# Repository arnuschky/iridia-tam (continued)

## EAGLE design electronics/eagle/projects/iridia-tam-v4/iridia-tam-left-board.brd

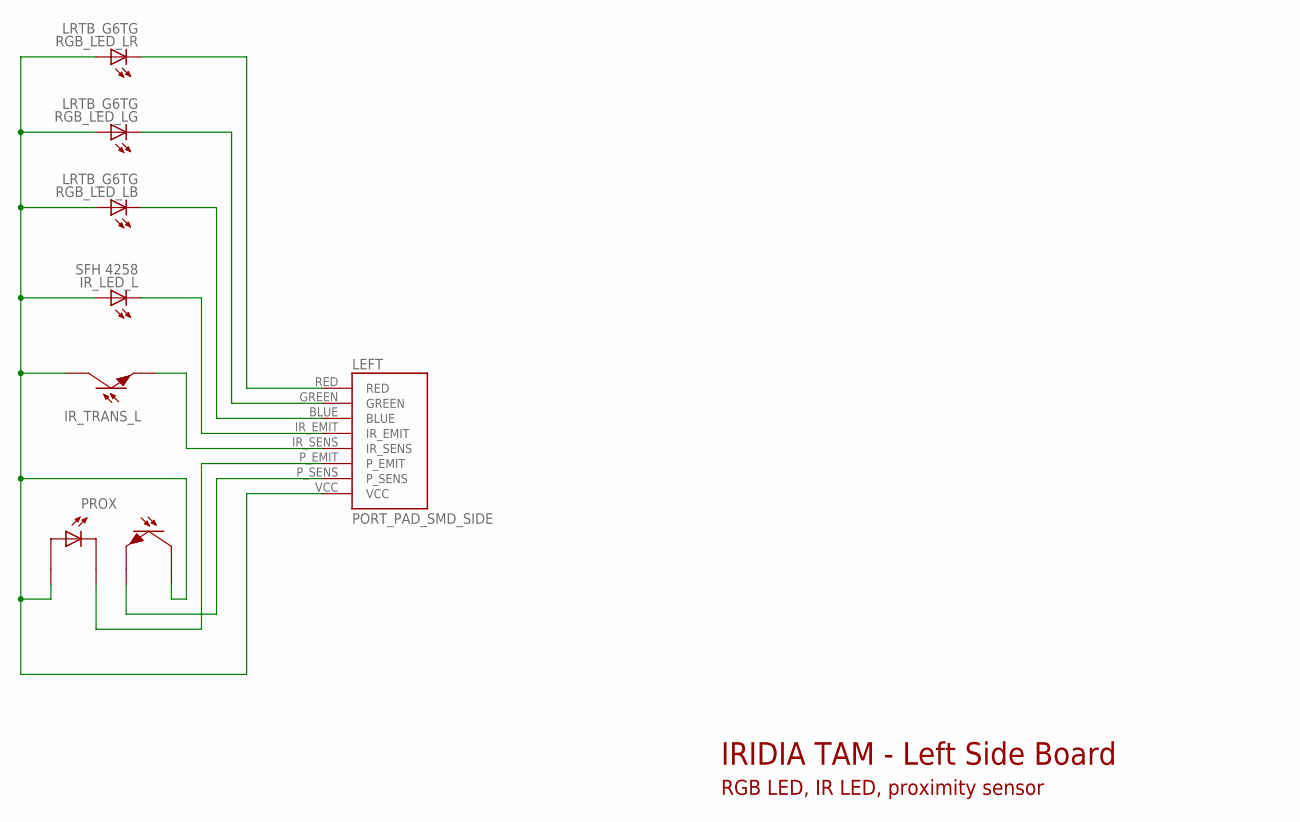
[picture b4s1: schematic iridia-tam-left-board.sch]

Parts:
IR_LED_L: SFH 4258; P-LCC-4-1C-3A
IR_TRANS_L: SFH 320 FA; P-LCC-2-TRANS
LEFT: PORT_PAD_SMD_SIDE
PROX: TCRT1000; TCRT1000_TH
RGB_LED_L: LRTB_G6TG; P-LCC-6_TOPLED

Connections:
BLUE_L: LEFT.BLUE, RGB_LED_L.C3 (C)
GREEN_L: LEFT.GREEN, RGB_LED_L.C2 (C)
IR_EMIT_L: IR_LED_L.C@1 (C), LEFT.IR_EMIT
IR_SENSE_L: IR_TRANS_L.E, LEFT.IR_SENS
PROX_EMIT: LEFT.P_EMIT, PROX.CAT
PROX_SENSE: LEFT.P_SENS, PROX.E
RED_L: LEFT.RED, RGB_LED_L.C1 (C)
VCC: IR_LED_L.A@2 (A), IR_LED_L.A@3 (A), IR_LED_L.A@4 (A), IR_TRANS_L.COL, LEFT.VCC, PROX.A, PROX.COL, RGB_LED_L.A1 (A), RGB_LED_L.A2 (A), RGB_LED_L.A3 (A)

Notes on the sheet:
IRIDIA TAM - Left Side Board
RGB LED, IR LED, proximity sensor

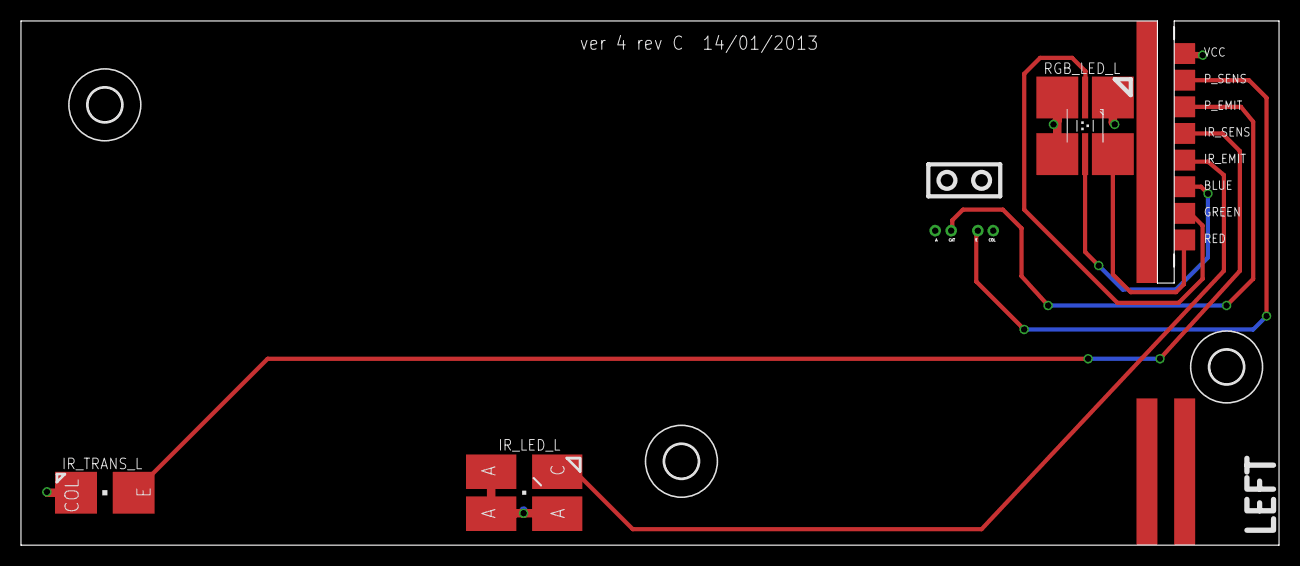
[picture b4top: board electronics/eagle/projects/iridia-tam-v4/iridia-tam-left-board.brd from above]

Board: 2 copper layers, 120.0 x 50.0 mm, 8 parts (0 on the bottom side), 8 nets.

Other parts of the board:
U$1, U$2, U$3: 3,2

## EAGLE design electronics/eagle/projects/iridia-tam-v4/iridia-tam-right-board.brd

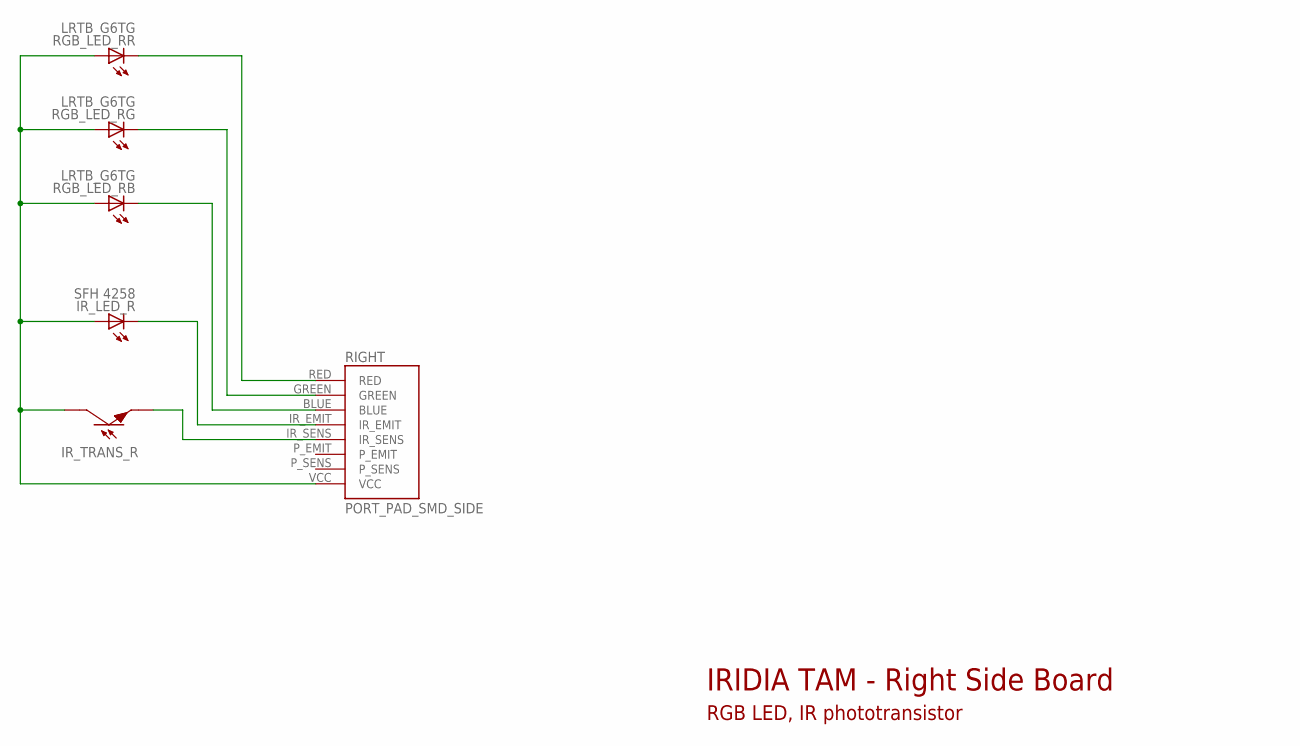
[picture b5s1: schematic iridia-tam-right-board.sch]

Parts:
IR_LED_R: SFH 4258; P-LCC-4-1C-3A
IR_TRANS_R: SFH 320 FA; P-LCC-2-TRANS
RGB_LED_R: LRTB_G6TG; P-LCC-6_TOPLED
RIGHT: PORT_PAD_SMD_SIDE

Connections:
BLUE_R: RGB_LED_R.C3 (C), RIGHT.BLUE
GREEN_R: RGB_LED_R.C2 (C), RIGHT.GREEN
IR_EMIT_R: IR_LED_R.C@1 (C), RIGHT.IR_EMIT
IR_SENSE_R: IR_TRANS_R.E, RIGHT.IR_SENS
RED_R: RGB_LED_R.C1 (C), RIGHT.RED
VCC: IR_LED_R.A@2 (A), IR_LED_R.A@3 (A), IR_LED_R.A@4 (A), IR_TRANS_R.COL, RGB_LED_R.A1 (A), RGB_LED_R.A2 (A), RGB_LED_R.A3 (A), RIGHT.VCC

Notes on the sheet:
IRIDIA TAM - Right Side Board
RGB LED, IR phototransistor

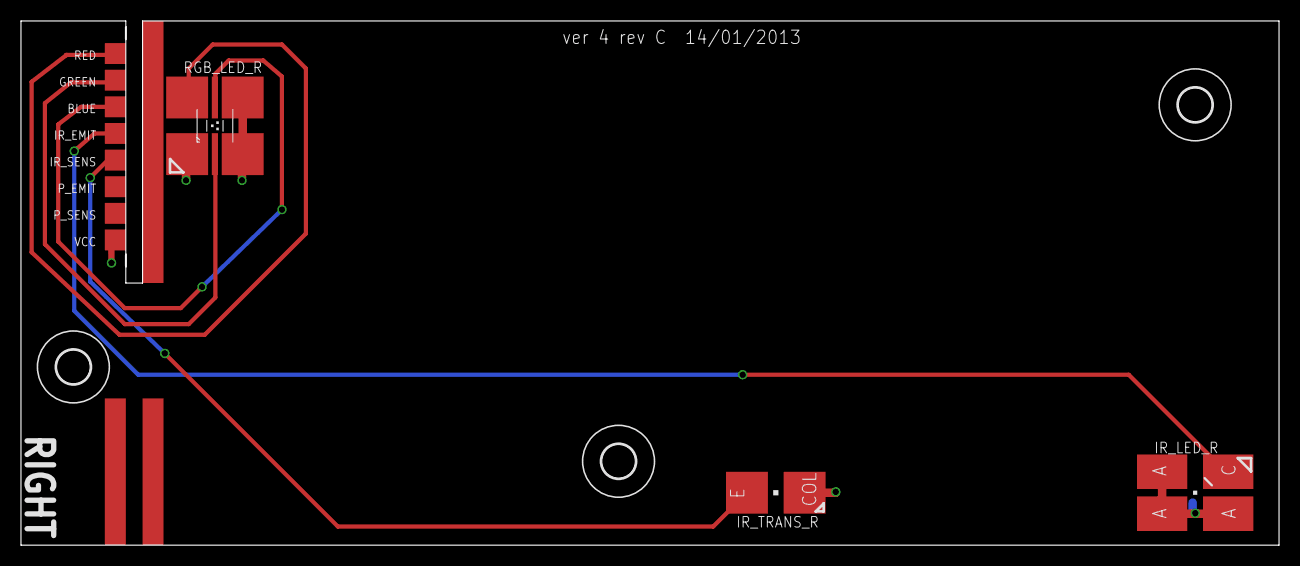
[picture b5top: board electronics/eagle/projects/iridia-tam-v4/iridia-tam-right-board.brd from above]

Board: 2 copper layers, 120.0 x 50.0 mm, 7 parts (0 on the bottom side), 6 nets.

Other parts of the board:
U$1, U$2, U$3: 3,2

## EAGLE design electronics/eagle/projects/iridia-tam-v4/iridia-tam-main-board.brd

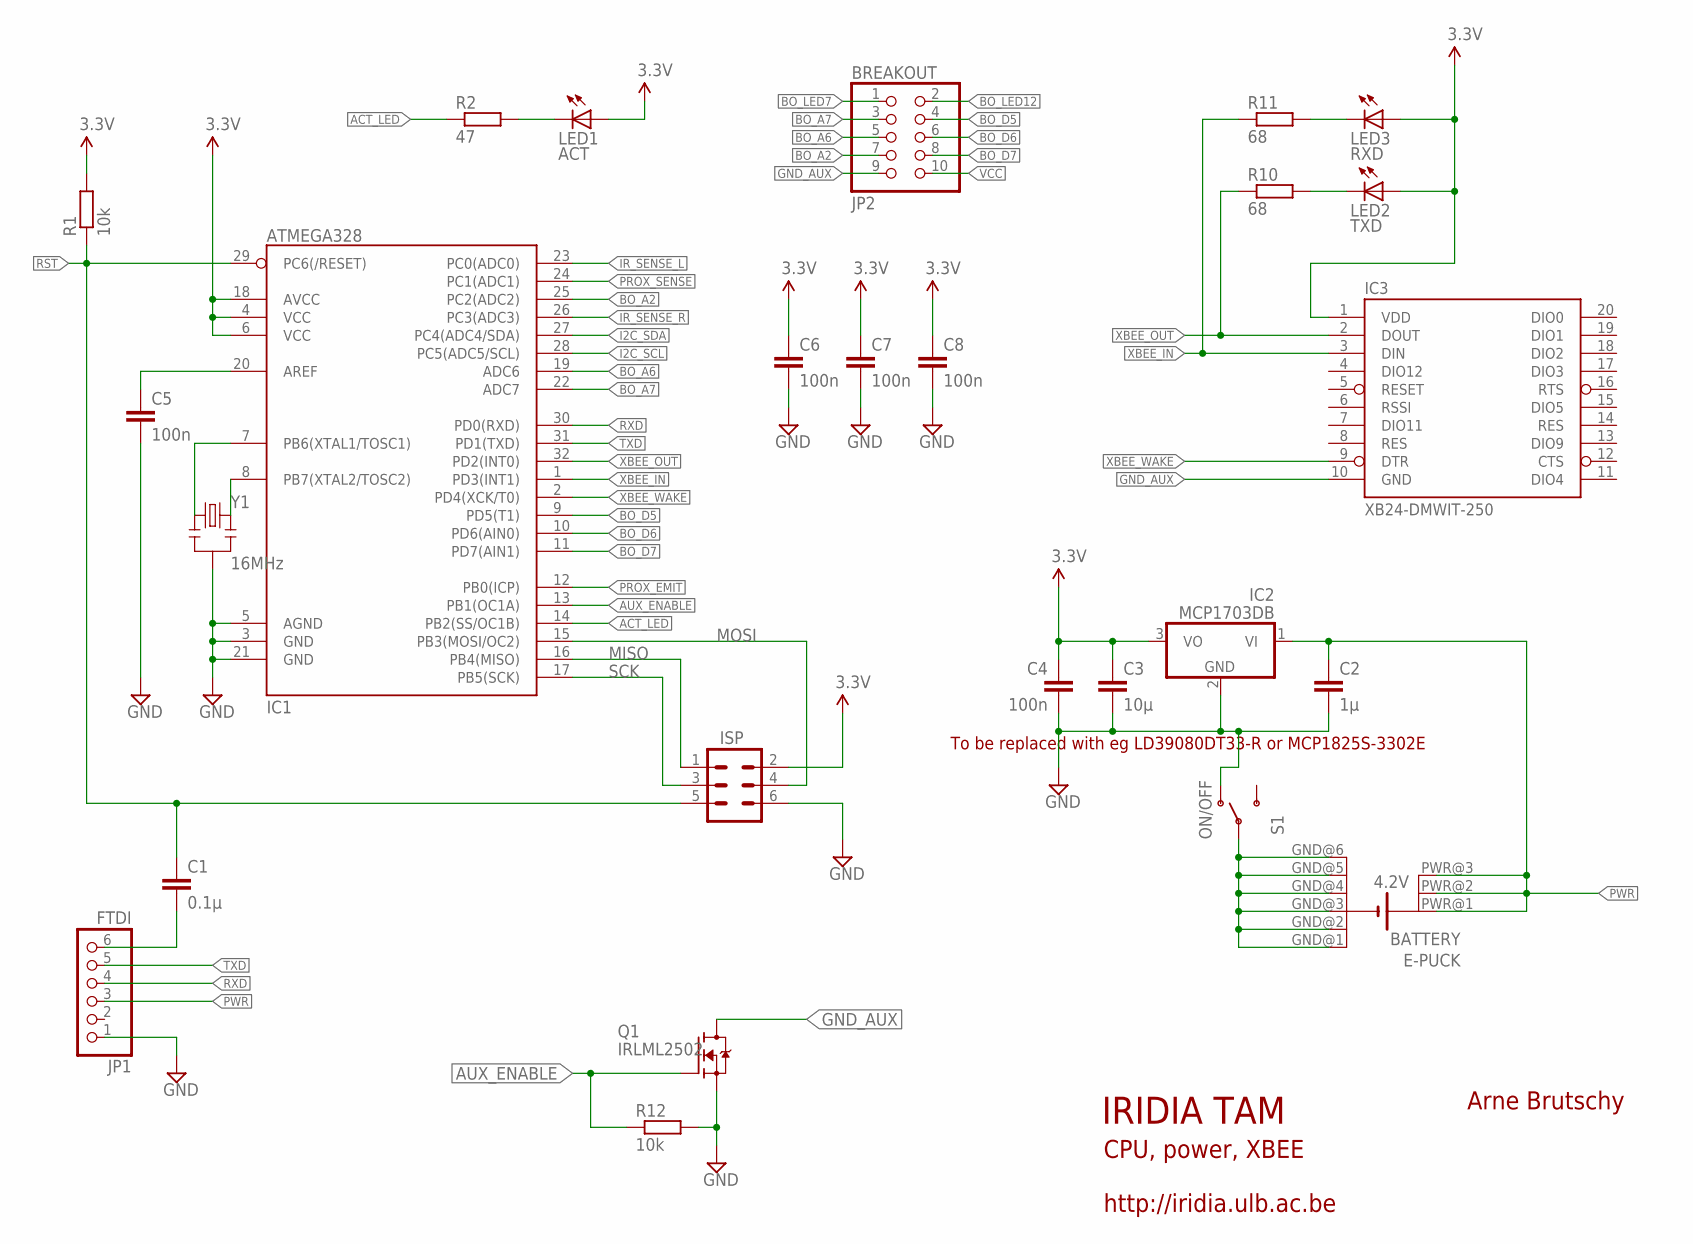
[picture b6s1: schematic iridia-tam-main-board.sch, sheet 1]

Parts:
BREAKOUT: JP2; 2X05SMD
C1: 0.1µ; 0805
C2: 1µ; 0805
C3: 10µ; 0805
C4, C5, C6, C7, C8: 100n; 0805
IC1: ATMEGA328; TQFP32-08
IC2: MCP1703DB; SOT223
IC3: XB24-DMWIT-250; XBEE-SMD
JP1: FTDI; 1X06SMD/90
LED1: ACT; LED-1206
LED2: TXD; CHIPLED_0805
LED3: RXD; CHIPLED_0805
Q1: IRLML2502; SOT23-3
R1, R12: 10k; R0805
R2: 47; R0805
R10, R11: 68; R0805
S1: ON/OFF; 200USP1T1A1M6RE
SV1: ISP; MA03-2
U$4: EPUCK_BATTERY
Y1: 16MHz; RESONATOR-SMD

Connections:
ACT_LED: IC1.14 (PB2(SS/OC1B)), R2.1
AUX_ENABLE: IC1.13 (PB1(OC1A)), Q1.1 (G), R12.1
BO_A2: BREAKOUT.7, IC1.25 (PC2(ADC2))
BO_A6: BREAKOUT.5, IC1.19 (ADC6)
BO_A7: BREAKOUT.3, IC1.22 (ADC7)
BO_D5: BREAKOUT.4, IC1.9 (PD5(T1))
BO_D6: BREAKOUT.6, IC1.10 (PD6(AIN0))
BO_D7: BREAKOUT.8, IC1.11 (PD7(AIN1))
BO_LED7: BREAKOUT.1; also elsewhere on the board
BO_LED12: BREAKOUT.2; also elsewhere on the board
FTDI_RST: C1.2, JP1.6
GND: C2.2, C3.2, C4.2, C5.2, C6.2, C7.2, C8.2, IC1.3 (GND), IC1.5 (AGND), IC1.21 (GND), IC2.2 (GND), JP1.1, Q1.2 (S), R12.2, S1.A, SV1.6, Y1.2; also elsewhere on the board
GND_AUX: BREAKOUT.9, IC3.10 (GND), Q1.3 (D); also elsewhere on the board
GND_BATT: S1.COM, U$4.GND@1 (-1), U$4.GND@2 (-2), U$4.GND@3 (-3), U$4.GND@4 (-4), U$4.GND@5 (-5), U$4.GND@6 (-6)
I2C_SCL: IC1.28 (PC5(ADC5/SCL)); also elsewhere on the board
I2C_SDA: IC1.27 (PC4(ADC4/SDA)); also elsewhere on the board
IR_SENSE_L: IC1.23 (PC0(ADC0)); also elsewhere on the board
IR_SENSE_R: IC1.26 (PC3(ADC3)); also elsewhere on the board
MISO: IC1.16 (PB4(MISO)), SV1.1
MOSI: IC1.15 (PB3(MOSI/OC2)), SV1.4
unnamed: IC1.7 (PB6(XTAL1/TOSC1)), Y1.1
unnamed: C5.1, IC1.20 (AREF)
unnamed: IC1.8 (PB7(XTAL2/TOSC2)), Y1.3
unnamed: LED2.C, R10.2
unnamed: LED3.C, R11.2
unnamed: LED1.C, R2.2
PROX_EMIT: IC1.12 (PB0(ICP)); also elsewhere on the board
PROX_SENSE: IC1.24 (PC1(ADC1)); also elsewhere on the board
PWR: C2.1, IC2.1 (VI), JP1.3, U$4.PWR@1 (+1), U$4.PWR@2 (+2), U$4.PWR@3 (+3)
RST: C1.1, IC1.29 (PC6(/RESET)), R1.1, SV1.5; also elsewhere on the board
RXD: IC1.30 (PD0(RXD)), JP1.4
SCK: IC1.17 (PB5(SCK)), SV1.3
TXD: IC1.31 (PD1(TXD)), JP1.5
VCC: BREAKOUT.10, C3.1, C4.1, C6.1, C7.1, C8.1, IC1.4 (VCC), IC1.6 (VCC), IC1.18 (AVCC), IC2.3 (VO), IC3.1 (VDD), LED1.A, LED2.A, LED3.A, R1.2, SV1.2; also elsewhere on the board
XBEE_IN: IC1.1 (PD3(INT1)), IC3.3 (DIN), R11.1
XBEE_OUT: IC1.32 (PD2(INT0)), IC3.2 (DOUT), R10.1
XBEE_WAKE: IC1.2 (PD4(XCK/T0)), IC3.9 (DTR)

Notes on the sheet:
IRIDIA TAM
Arne Brutschy
http://iridia.ulb.ac.be
CPU, power, XBEE
To be replaced with eg LD39080DT33-R or MCP1825S-3302E

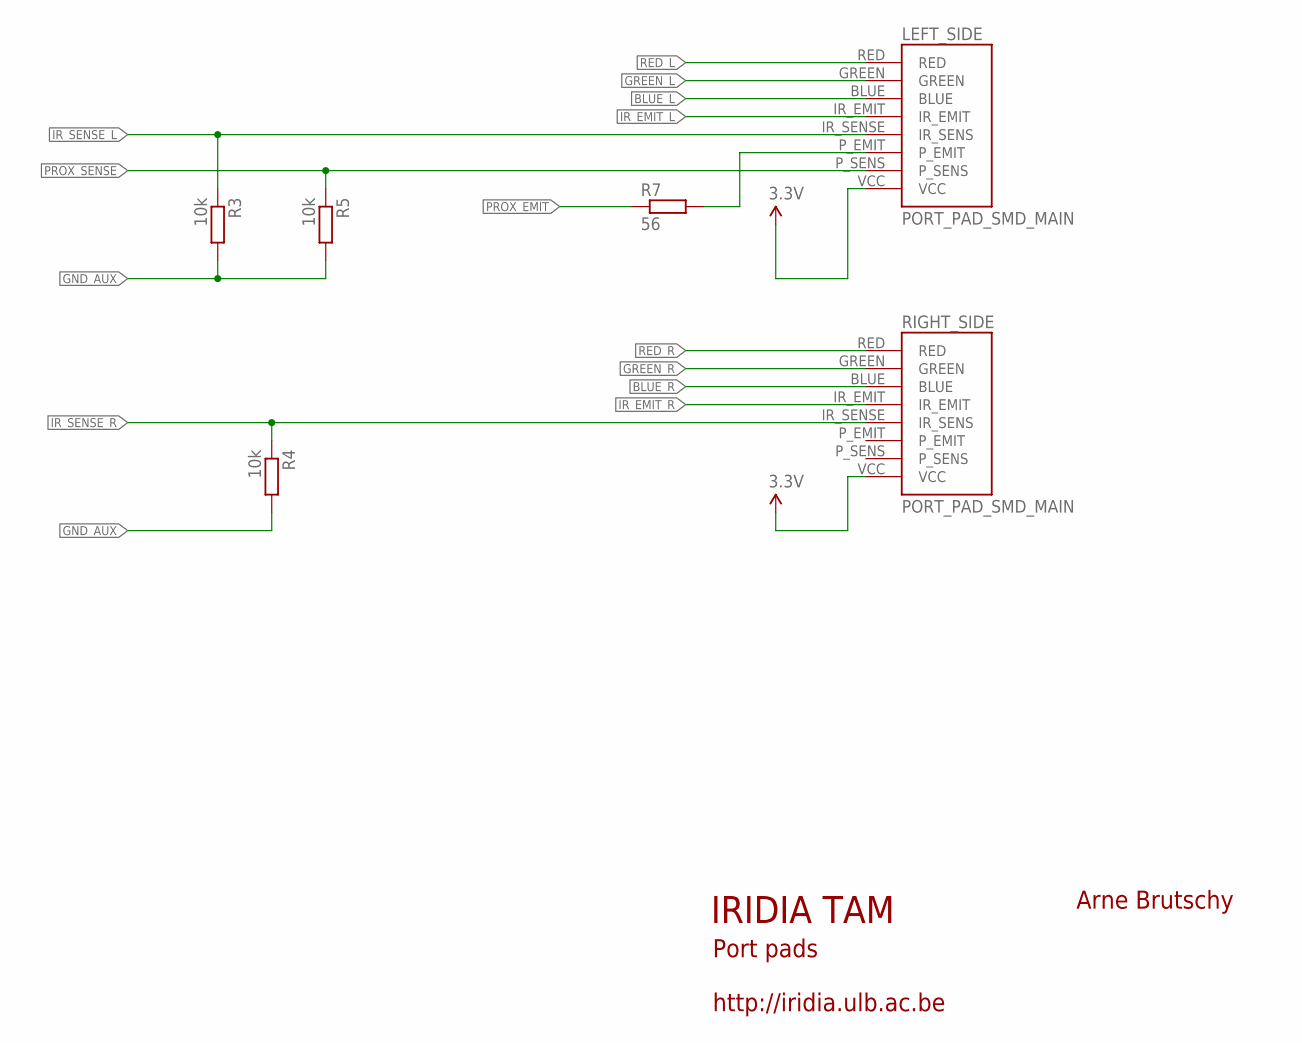
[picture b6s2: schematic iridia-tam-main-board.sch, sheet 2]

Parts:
LEFT_SIDE: PORT_PAD_SMD_MAIN
R3, R4, R5: 10k; R0805
R7: 56; R0805
RIGHT_SIDE: PORT_PAD_SMD_MAIN

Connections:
BLUE_L: LEFT_SIDE.BLUE; also elsewhere on the board
BLUE_R: RIGHT_SIDE.BLUE; also elsewhere on the board
GND_AUX: R3.2, R4.2, R5.2; also elsewhere on the board
GREEN_L: LEFT_SIDE.GREEN; also elsewhere on the board
GREEN_R: RIGHT_SIDE.GREEN; also elsewhere on the board
IR_EMIT_L: LEFT_SIDE.IR_EMIT; also elsewhere on the board
IR_EMIT_R: RIGHT_SIDE.IR_EMIT; also elsewhere on the board
IR_SENSE_L: LEFT_SIDE.IR_SENSE (IR_SENS), R3.1; also elsewhere on the board
IR_SENSE_R: R4.1, RIGHT_SIDE.IR_SENSE (IR_SENS); also elsewhere on the board
unnamed: LEFT_SIDE.P_EMIT, R7.2
PROX_EMIT: R7.1; also elsewhere on the board
PROX_SENSE: LEFT_SIDE.P_SENS, R5.1; also elsewhere on the board
RED_L: LEFT_SIDE.RED; also elsewhere on the board
RED_R: RIGHT_SIDE.RED; also elsewhere on the board
VCC: LEFT_SIDE.VCC, RIGHT_SIDE.VCC; also elsewhere on the board

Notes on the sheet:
IRIDIA TAM
Arne Brutschy
http://iridia.ulb.ac.be
Port pads

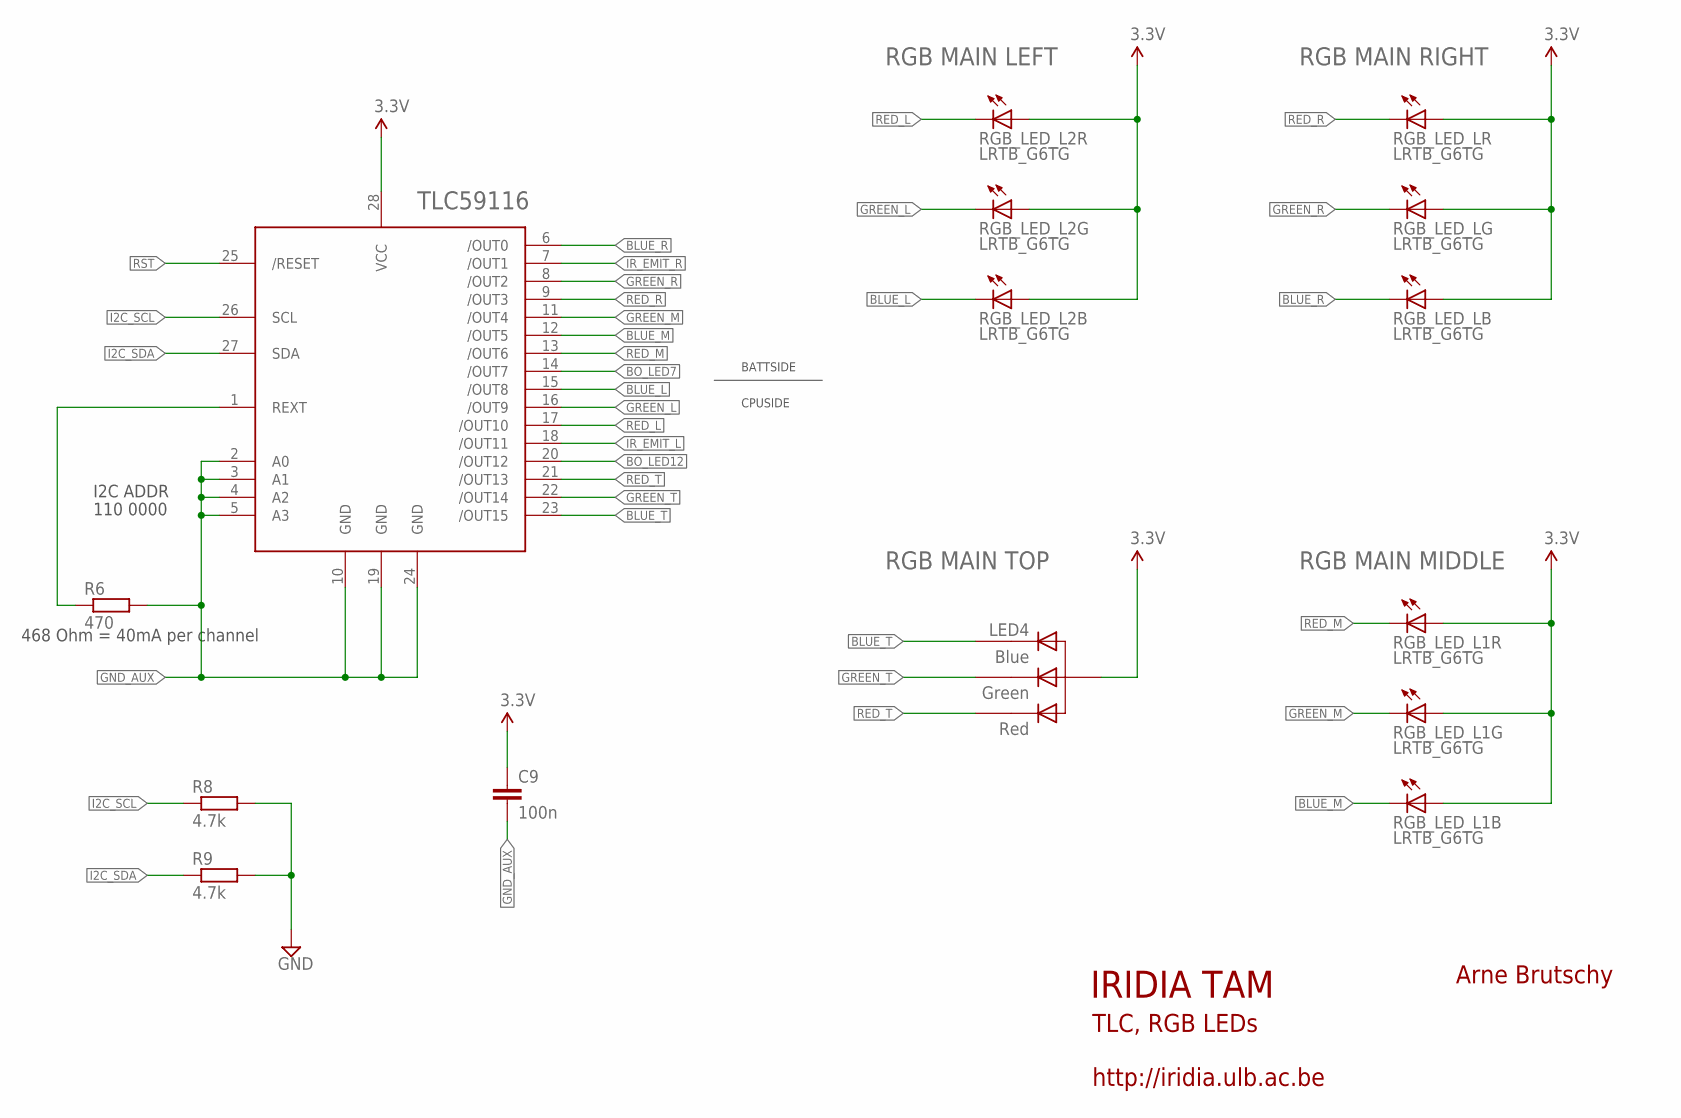
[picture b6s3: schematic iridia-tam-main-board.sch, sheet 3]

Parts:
C9: 100n; 0805
IC4: TLC59116; TSSOP28
LED4: RGBLED_CA5MMTROUGHHOLE; LED5MMRGB
R6: 470; R0805
R8, R9: 4.7k; R0805
RGB_LED_L, RGB_LED_L1, RGB_LED_L2: LRTB_G6TG; P-LCC-6_TOPLED

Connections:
BLUE_L: IC4.15 (/OUT8), RGB_LED_L2.C3 (C); also elsewhere on the board
BLUE_M: IC4.12 (/OUT5), RGB_LED_L1.C3 (C)
BLUE_R: IC4.6 (/OUT0), RGB_LED_L.C3 (C); also elsewhere on the board
BLUE_T: IC4.23 (/OUT15), LED4.4 (CB)
BO_LED7: IC4.14 (/OUT7); also elsewhere on the board
BO_LED12: IC4.20 (/OUT12); also elsewhere on the board
GND: R8.2, R9.2; also elsewhere on the board
GND_AUX: C9.2, IC4.2 (A0), IC4.3 (A1), IC4.4 (A2), IC4.5 (A3), IC4.10 (GND), IC4.19 (GND), IC4.24 (GND), R6.2; also elsewhere on the board
GREEN_L: IC4.16 (/OUT9), RGB_LED_L2.C2 (C); also elsewhere on the board
GREEN_M: IC4.11 (/OUT4), RGB_LED_L1.C2 (C)
GREEN_R: IC4.8 (/OUT2), RGB_LED_L.C2 (C); also elsewhere on the board
GREEN_T: IC4.22 (/OUT14), LED4.3 (CG)
I2C_SCL: IC4.26 (SCL), R8.1; also elsewhere on the board
I2C_SDA: IC4.27 (SDA), R9.1; also elsewhere on the board
IR_EMIT_L: IC4.18 (/OUT11); also elsewhere on the board
IR_EMIT_R: IC4.7 (/OUT1); also elsewhere on the board
RED_L: IC4.17 (/OUT10), RGB_LED_L2.C1 (C); also elsewhere on the board
RED_M: IC4.13 (/OUT6), RGB_LED_L1.C1 (C)
RED_R: IC4.9 (/OUT3), RGB_LED_L.C1 (C); also elsewhere on the board
RED_T: IC4.21 (/OUT13), LED4.1 (CR)
REXT: IC4.1 (REXT), R6.1
RST: IC4.25 (/RESET); also elsewhere on the board
VCC: C9.1, IC4.28 (VCC), LED4.2 (A), RGB_LED_L.A1 (A), RGB_LED_L.A2 (A), RGB_LED_L.A3 (A), RGB_LED_L1.A1 (A), RGB_LED_L1.A2 (A), RGB_LED_L1.A3 (A), RGB_LED_L2.A1 (A), RGB_LED_L2.A2 (A), RGB_LED_L2.A3 (A); also elsewhere on the board

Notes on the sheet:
IRIDIA TAM
Arne Brutschy
http://iridia.ulb.ac.be
TLC, RGB LEDs
TLC59116
RGB MAIN LEFT
RGB MAIN RIGHT
RGB MAIN MIDDLE
RGB MAIN TOP
I2C ADDR
110 0000
468 Ohm = 40mA per channel
BATTSIDE
CPUSIDE

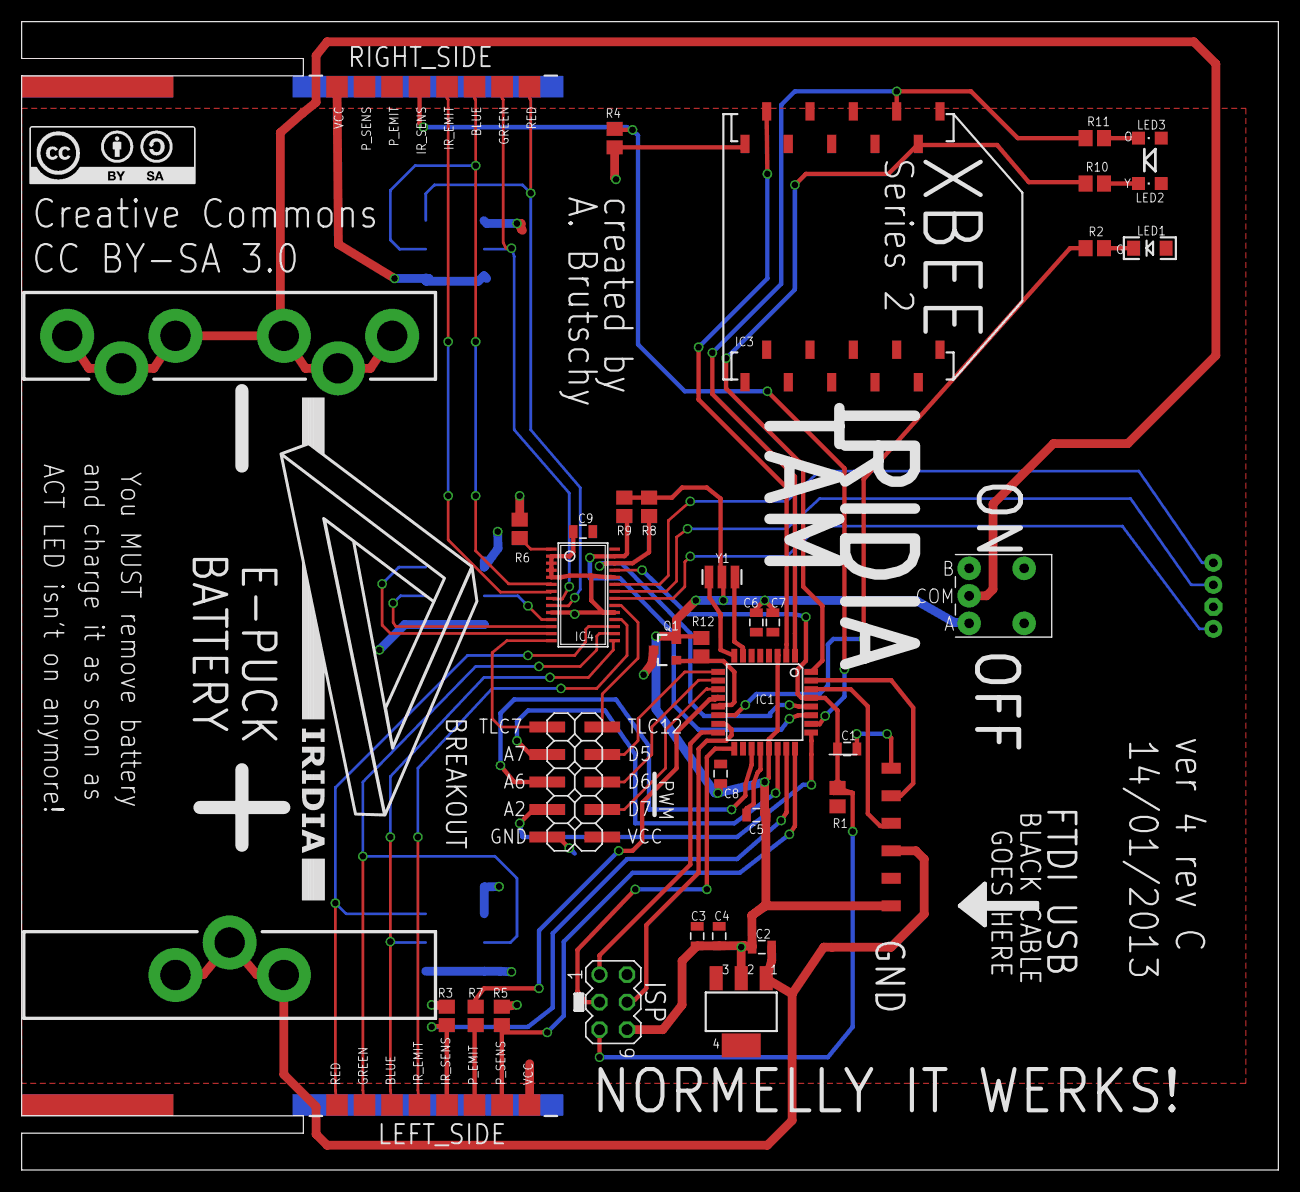
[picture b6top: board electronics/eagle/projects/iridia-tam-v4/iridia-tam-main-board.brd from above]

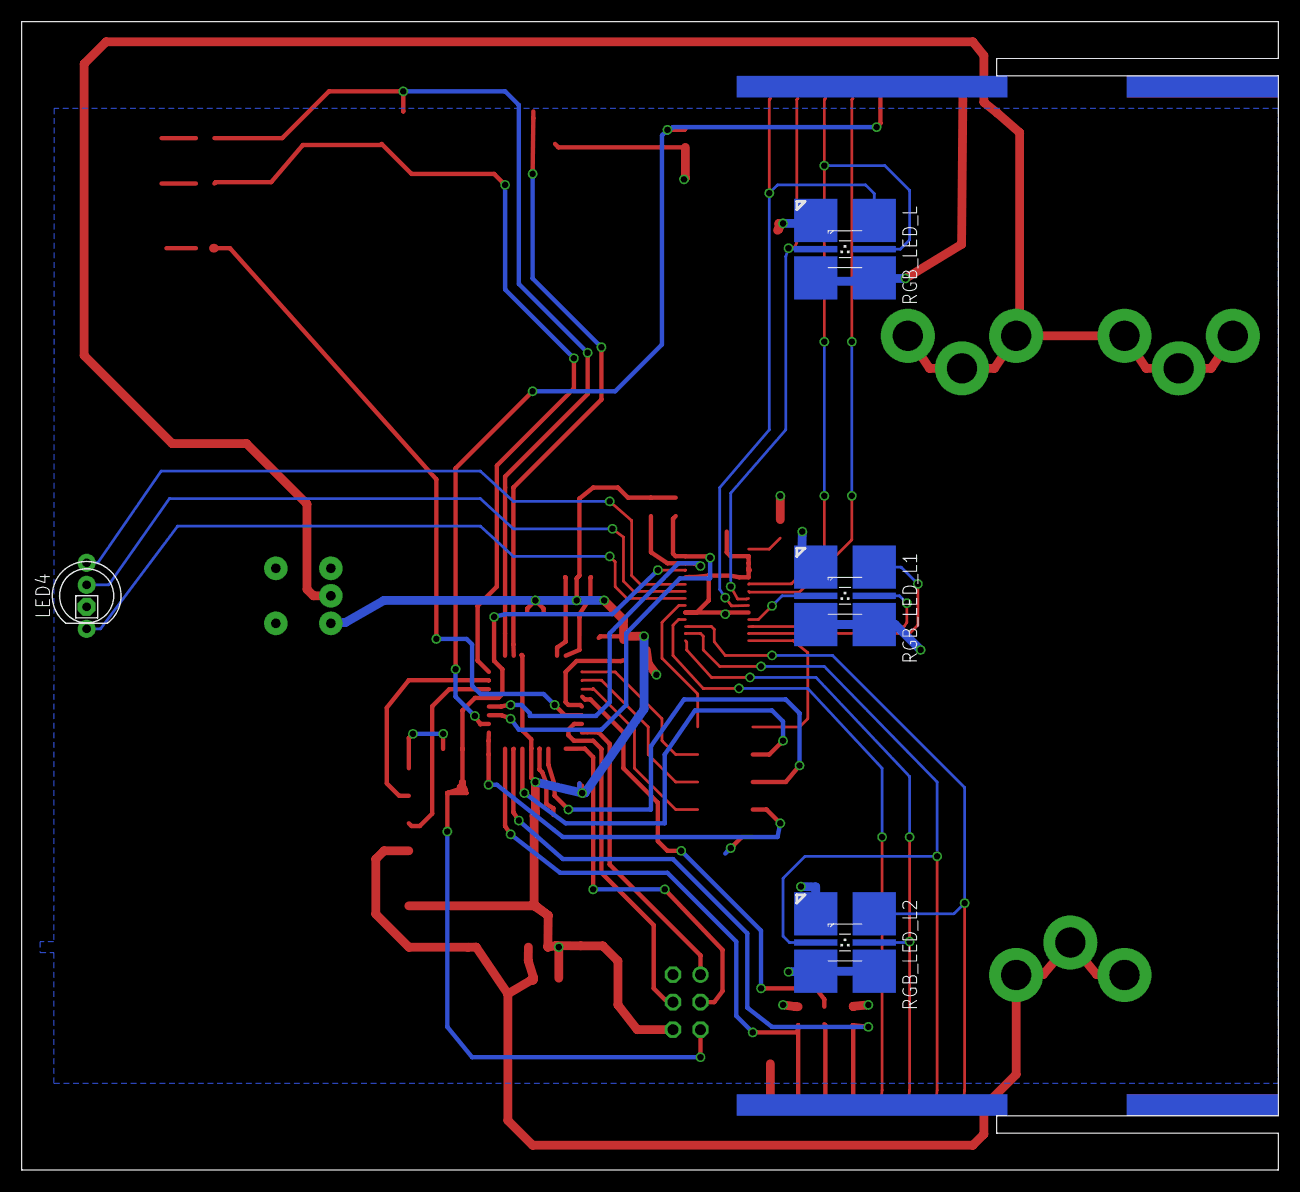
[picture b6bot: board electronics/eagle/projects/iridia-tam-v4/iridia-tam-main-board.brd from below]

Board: 2 copper layers, 116.0 x 106.0 mm, 41 parts (4 on the bottom side), 53 nets.

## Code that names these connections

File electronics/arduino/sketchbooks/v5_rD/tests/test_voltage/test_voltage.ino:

/********************************************************************
 *
 * Example Arduino Controller for the IRIDIA TAM v5 revA
 *
 ********************************************************************/

/**
 * Debug macros which enable bits of code used for debugging the firmware.
 */
#define DEBUG_ENABLE_SERIAL_OUTPUT    // disabled all serial printout and strings

/**
 * Controls which messages are logged.
 */
// general output classes
#define P_INFO(format, ...) p( "[INFO] %05d " format, cycle, ## __VA_ARGS__ )
//#define P_INFO(format, ...)
#define P_WARN(format, ...) p( "[WARN] %04d " format, cycle, ## __VA_ARGS__ )
//#define P_INFO(format, ...)


/**
 * Definition of hardware pins. Do NOT change this.
 */
#define XBEE_WAKE_PIN     12  // unused at the moment
#define XBEE_CTS_PIN      13  // unused at the moment
#define XBEE_RTS_PIN      18  // unused at the moment
#define XBEE_RST_PIN      15  // unused at the moment

#define POWER_OFF_PIN      3  // all-mighty power-off pin for PSU
#define VBATT_SENSE_PIN   A1  // signal VBATT_SENSE

#define PROX_SENSE_PIN    14  // ICP pin fixed to internal Timer
#define PROX_EMIT_PIN      1

#define IRB_SENSE_PIN     A2  // signal IR_SENSE_L
#define IRF_SENSE_PIN     A0  // signal IR_SENSE_R


/**
 * Global variables
 */

// count of control cycles, each cycle = 0.1 secs
unsigned long cycle = 0;

/**
 * Small helper function that emulates printf().
 * Disabled by DEBUG_ENABLE_SERIAL_OUTPUT.
 * @param fmt  format string, followed by possible parameters
 */
void p(const char *fmt, ... )
{
#ifdef DEBUG_ENABLE_SERIAL_OUTPUT
  char tmp[128]; // resulting string limited to 128 chars
  va_list args;
  va_start(args, fmt );
  vsnprintf(tmp, 128, fmt, args);
  va_end (args);
  Serial.print(tmp);
#else
#endif
}

/**
 * Prepare serial and set necessary digital pins to output.
 * Also initializes the Xbee module and resolves the address of the coordinator.
 */
void setup()
{
  Serial.begin(57600);

  pinMode(VBATT_SENSE_PIN, INPUT);
  pinMode(POWER_OFF_PIN, OUTPUT);
  digitalWrite(POWER_OFF_PIN, LOW);

  p("IRIDIA TAM initialization OK\n\n");
}

/**************************************************************************************
 *
 * Main loop. Loops every CYCLE_LENGTH ms.
 *
 **************************************************************************************/

int emptyBattCycles = 0;

void loop()
{
  // every second
  if (cycle % 10 == 0) {
    int vBatt = analogRead(VBATT_SENSE_PIN) * 33;
     p("[DEBUG] Reading battery voltage: %d.%03d V\n", (vBatt / 1000), (vBatt % 1000));

    if (vBatt <= 2700) {
      P_WARN("Battery empty!\n");
      emptyBattCycles++;
    }  
    else if (vBatt <= 3000) {
      P_WARN("Battery low!\n");
    }
    else {
      emptyBattCycles = 0;
    }  
  }
  
  if (emptyBattCycles == 10) {
    P_WARN("Battery empty, shutting down!\n");
    delay(1000);
    P_WARN("Shutting down now.\n");
    delay(500);
    digitalWrite(POWER_OFF_PIN, HIGH);
    delay(500);
  }

  delay(100);

  cycle++;
} 

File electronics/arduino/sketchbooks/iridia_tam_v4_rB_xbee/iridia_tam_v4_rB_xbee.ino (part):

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/**
 * Definition of hardware pins. Do NOT change this.
 */
#define XBEE_IN          3  // xbee serial pins
#define XBEE_OUT         2  // accessed via softserial
#define XBEE_WAKE        4  // xbee wakeup pin (unused at the moment)

#define LED_ACT_PIN     10  // activity LED pin (HIGH = led off!)

#define AUX_ENABLE_PIN   9  // all-mighty enable pin for the auxillary devices

#define PROX_SENSE_PIN  A1  //
#define PROX_EMIT_PIN    8  // D8, pin 12

#define IRB_SENSE_PIN   A3  // signal IR_SENSE_L
#define IRF_SENSE_PIN   A0  // signal IR_SENSE_R

// pin definitions of the LEDs connected to the TLC
enum TlcLedPins {
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  memset(&lastReportedState, sizeof(state_t), 0);

  // switch on aux devices (TLC, XBEE, sensors)
  pinMode(AUX_ENABLE_PIN, OUTPUT);
  digitalWrite(AUX_ENABLE_PIN, HIGH);

  //
  // Aux devices init (TLC and sensors)
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  pinMode(IRB_SENSE_PIN, INPUT);

  // emit and sensing for proximity sensor
  pinMode(PROX_EMIT_PIN, OUTPUT);
  digitalWrite(PROX_EMIT_PIN, HIGH);
  pinMode(PROX_SENSE_PIN, INPUT);

  //
  // Xbee initialization
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void shutdown()
{
  // switch off all aux devices (TLC, XBEE, sensors)
  pinMode(AUX_ENABLE_PIN, OUTPUT);
  digitalWrite(AUX_ENABLE_PIN, LOW);

  // switch off activity LED
  activityLed(false);
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
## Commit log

2013-02-19 Create gh-pages branch via GitHub
2013-02-19 Added links to readme, corrected header
2013-04-03 Added coordinator, eagle files, 3d model files, and photos
2013-04-03 Removed some unnecessary files from the coordinator
2013-04-03 Removed outdated gerbers
2014-01-13 Updated to final version 5 revision D
2014-01-13 Fixing readme
2014-01-14 Updated BOMs
2014-01-14 Some readme fixes
2014-01-14 Started editing index html
2014-01-14 Fixing heading again
2014-01-14 Wrote git pages
2014-01-20 Added Anthony to list of contribs
2014-01-20 Updates coordinator to match PoC experiment
2014-03-11 Added new photos of the TAM
2014-03-11 Added new photos
2014-03-11 Corrected author order
2014-08-28 Minor fixes in bom
2014-08-28 Updated coordinator to be compatible with ARGoS
